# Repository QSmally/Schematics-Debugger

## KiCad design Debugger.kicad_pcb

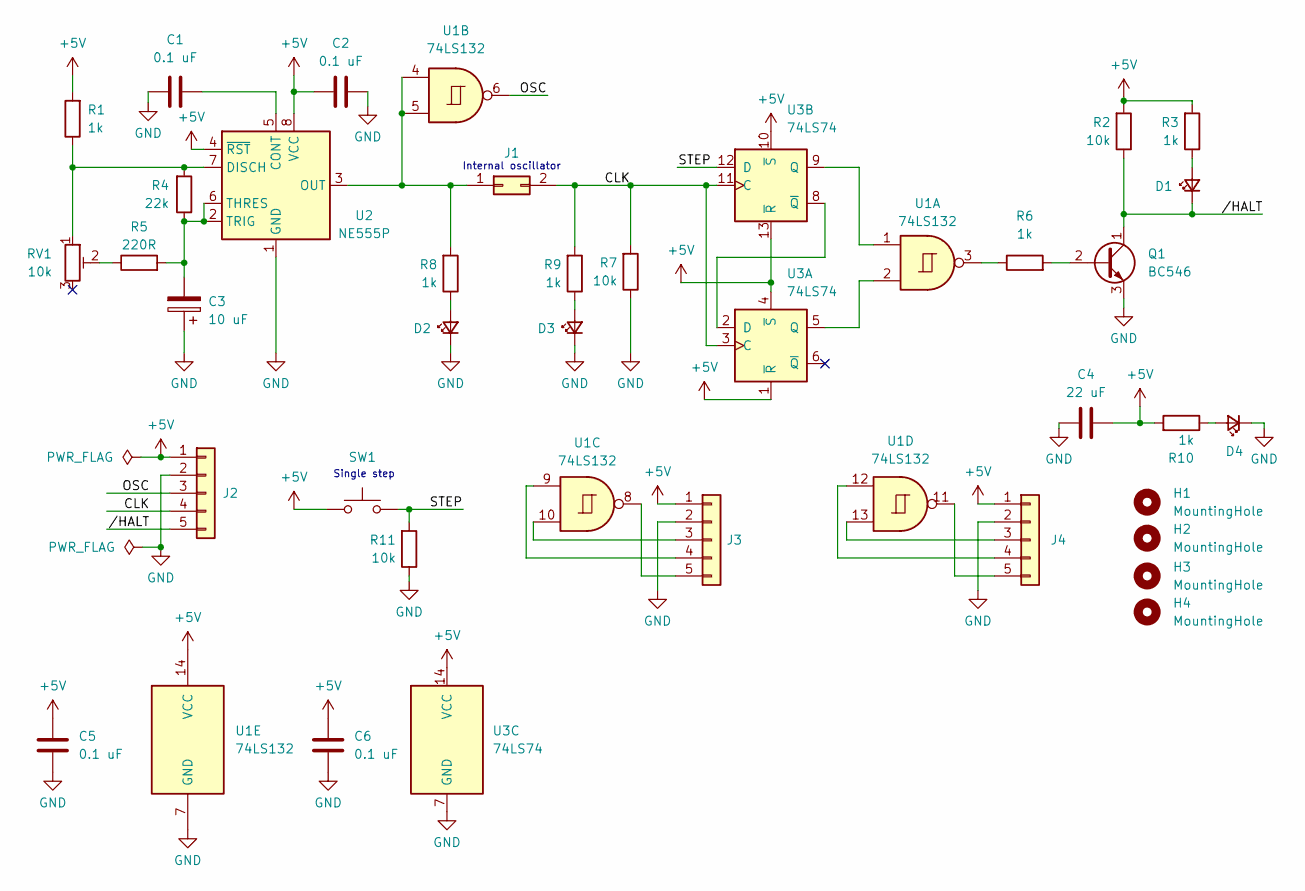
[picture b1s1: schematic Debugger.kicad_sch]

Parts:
C1, C2, C5, C6: 0.1 uF; C_0603_1608Metric
C3: 10 uF; CP_Radial_D4.0mm_P2.00mm
C4: 22 uF; C_0805_2012Metric
D1, D2, D3: LED Green; LED_0603_1608Metric
D4: LED Red; LED_0603_1608Metric
H1, H2, H3, H4: MountingHole; MountingHole_2.2mm_M2_DIN965_Pad
J1: male; PinHeader_2x01_P2.54mm_Vertical
J2, J3, J4: male; PinHeader_1x05_P2.54mm_Vertical
Q1: BC546; TO-92_Inline
R1, R3, R6, R8, R9, R10: 1k; R_0603_1608Metric
R2, R7, R11: 10k; R_0603_1608Metric
R4: 22k; R_0603_1608Metric
R5: 220R; R_0603_1608Metric
RV1: 10k; Potentiometer_ACP_CA9-V10_Vertical
SW1: push button; SW_PUSH_6mm
U1: 74LS132; DIP-14_W7.62mm_Socket
U2: NE555P; DIP-8_W7.62mm_Socket
U3: 74LS74; DIP-14_W7.62mm_Socket

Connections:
+5V: C2.2, C4.1, C5.2, C6.2, J2.1, J3.1, J4.1, R1.2, R2.2, R3.2, R10.2, SW1.1, U1.14 (VCC), U2.4 (~RST), U2.8 (VCC), U3.1 (~R), U3.4 (~S), U3.10 (~S), U3.13 (~R), U3.14 (VCC)
/CLK: J1.2, J2.4, R7.2, R9.2, U3.3 (C), U3.11 (C)
/OSC: J2.3, U1.6
/STEP: R11.2, SW1.2, U3.12 (D)
//HALT: D1.1 (K), J2.5, Q1.1 (C), R2.1
GND: C1.1, C2.1, C3.1, C4.2, C5.1, C6.1, D2.1 (K), D3.1 (K), D4.1 (K), J2.2, J3.2, J4.2, Q1.3 (E), R7.1, R11.1, U1.7 (GND), U2.1 (GND), U3.7 (GND)
unnamed: D1.2 (A), R3.1
unnamed: D2.2 (A), R8.1
unnamed: D3.2 (A), R9.1
unnamed: D4.2 (A), R10.1
unnamed: J1.1, R8.2, U1.4, U1.5, U2.3 (OUT)
unnamed: J3.3, U1.10
unnamed: J3.4, U1.9
unnamed: J3.5, U1.8
unnamed: J4.3, U1.13
unnamed: J4.4, U1.12
unnamed: J4.5, U1.11
unnamed: Q1.2 (B), R6.2
unnamed: R5.1, RV1.2
unnamed: R6.1, U1.3
unnamed: C1.2, U2.5 (CONT)
unnamed: R1.1, R4.2, RV1.1, U2.7 (DISCH)
unnamed: C3.2, R4.1, R5.2, U2.2 (TRIG), U2.6 (THRES)
unnamed: U3.2 (D), U3.8 (~Q)
unnamed: U1.2, U3.5 (Q)
unnamed: U1.1, U3.9 (Q)

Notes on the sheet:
Single step
Internal oscillator

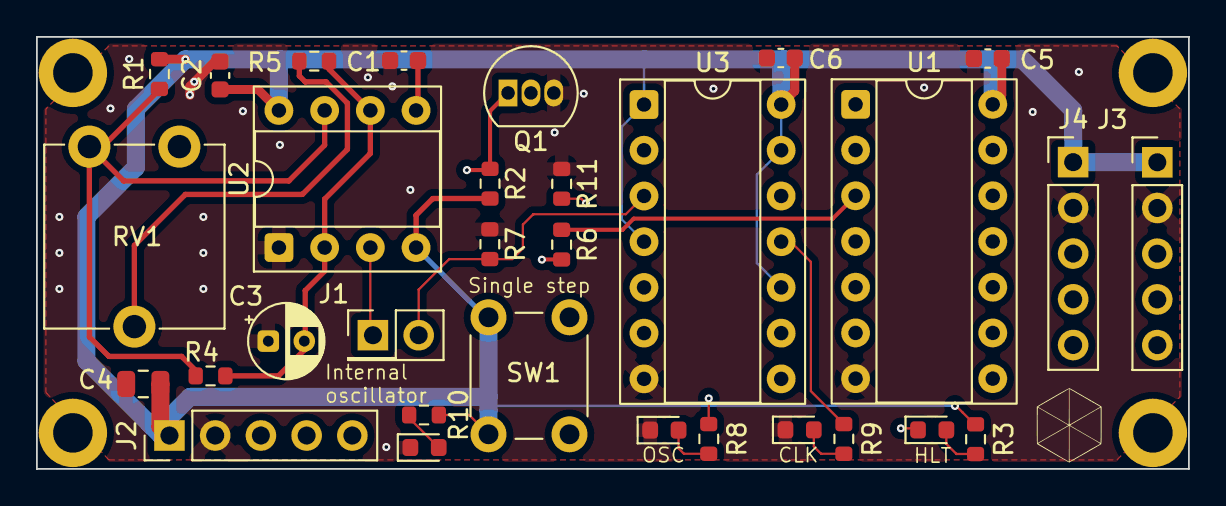
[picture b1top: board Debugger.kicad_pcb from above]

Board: 4 copper layers, 64.0 x 24.0 mm, 35 parts (0 on the bottom side), 26 nets.

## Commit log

2026-04-21 Project: initial commit
2026-04-22 Schematic: schmitt trigger, auxilary ports
2026-05-14 Schematic: fix power flag
2026-05-14 Board: add PCB drawing
2026-05-15 Schematic, Board: fix D1 LED
2026-05-16 Board: input header consistency
2026-05-16 Board: revision 2
2026-05-17 Board, Gerber: fail-safe pot resistor, production
